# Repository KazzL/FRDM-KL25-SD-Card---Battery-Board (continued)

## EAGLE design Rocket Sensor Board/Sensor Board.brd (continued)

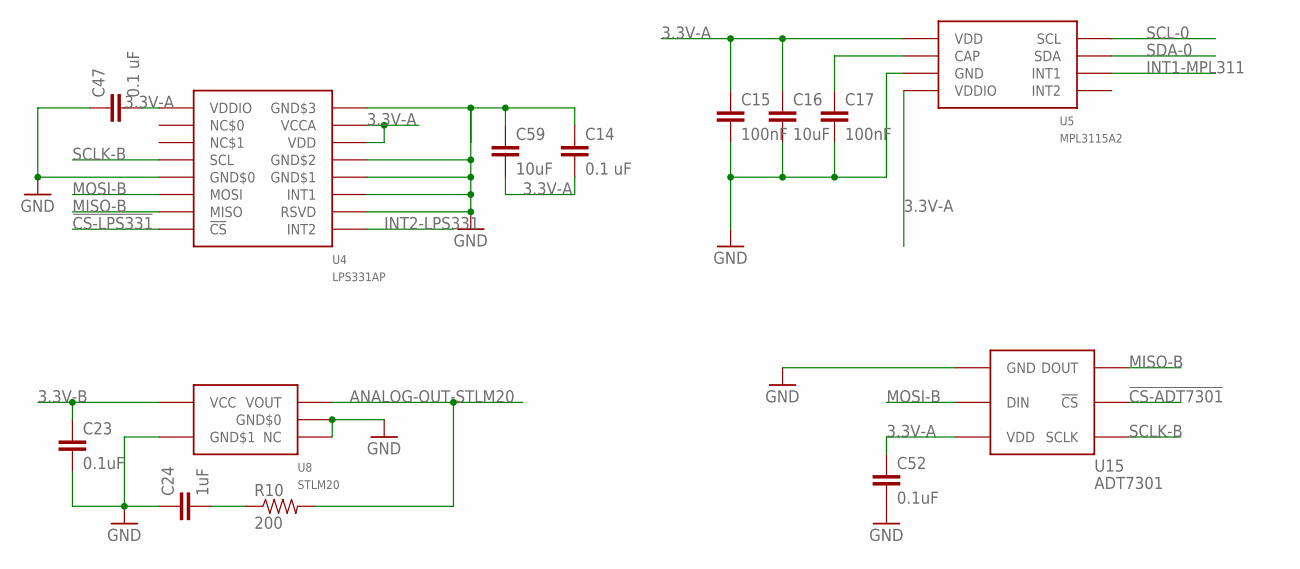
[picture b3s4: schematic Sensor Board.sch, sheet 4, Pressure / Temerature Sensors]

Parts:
C14, C47: 0.1 uF; C0402
C15, C17: 100nF; C0402
C16: 10uF; C0402
C23, C52: 0.1uF; C0402
C24: 1uF; C0402
C59: 10uF; C0603
R10: 200; R0402
U4: LPS331AP; LGA-16(3X3)
U5: MPL3115A2; LGA-8(5X3)
U8: STLM20; SOT323-5L
U15: ADT7301; SOT23-6

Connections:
3.3V-A: C14.2, C15.1, C16.1, C47.2, C52.1, C59.2, U4.P$1 (VDDIO), U4.P$14 (VDD), U4.P$15 (VCCA), U5.P$1 (VDD), U5.P$4 (VDDIO), U15.P$3 (VDD); also elsewhere on the board
3.3V-B: C23.1, U8.P$4 (VCC); also elsewhere on the board
!CS-ADT7301: U15.P$5 (!CS); also elsewhere on the board
!CS-LPS331: U4.P$8 (!CS); also elsewhere on the board
ANALOG-OUT-STLM20: R10.2, U8.P$3 (VOUT); also elsewhere on the board
GND: C14.1, C15.2, C16.2, C17.2, C23.2, C24.1, C47.1, C52.2, C59.1, U4.P$5 (GND$0), U4.P$10 (RSVD), U4.P$11 (INT1), U4.P$12 (GND$1), U4.P$13 (GND$2), U4.P$16 (GND$3), U5.P$3 (GND), U8.P$1 (NC), U8.P$2 (GND$0), U8.P$5 (GND$1), U15.P$1 (GND); also elsewhere on the board
INT1-MPL311: U5.P$6 (INT1); also elsewhere on the board
INT2-LPS331: U4.P$9 (INT2); also elsewhere on the board
MISO-B: U4.P$7 (MISO), U15.P$6 (DOUT); also elsewhere on the board
MOSI-B: U4.P$6 (MOSI), U15.P$2 (DIN); also elsewhere on the board
unnamed: C17.1, U5.P$2 (CAP)
unnamed: C24.2, R10.1
SCL-0: U5.P$8 (SCL); also elsewhere on the board
SCLK-B: U4.P$4 (SCL), U15.P$4 (SCLK); also elsewhere on the board
SDA-0: U5.P$7 (SDA); also elsewhere on the board

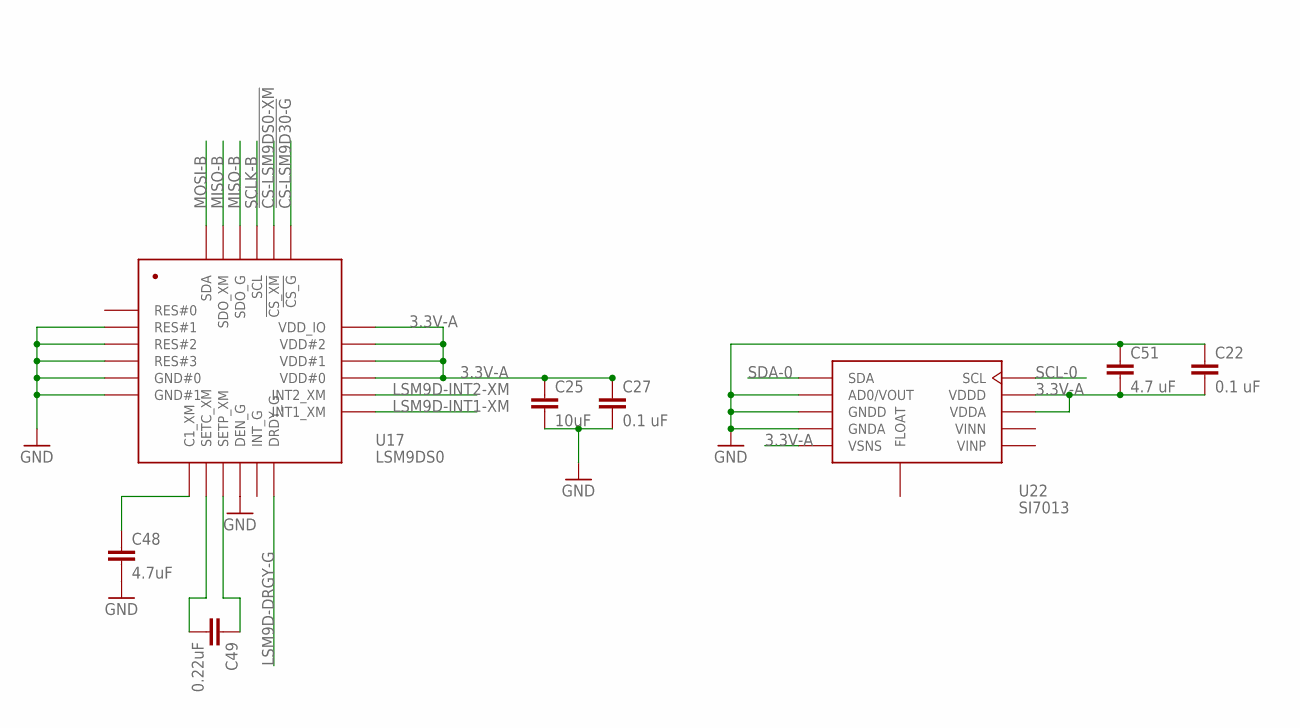
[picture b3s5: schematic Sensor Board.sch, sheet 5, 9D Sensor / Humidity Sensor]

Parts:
C22, C27: 0.1 uF; C0402
C25: 10uF; C0603
C48: 4.7uF; C0603
C49: 0.22uF; C0402
C51: 4.7 uF; C0402
U17: LSM9DS0; LGA-24(4X4)
U22: SI7013; DFN-10(3X3)

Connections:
3.3V-A: C22.2, C25.1, C27.1, C51.2, U17.P$15 (VDD#0), U17.P$16 (VDD#1), U17.P$17 (VDD#2), U17.P$18 (VDD_IO), U22.P$5 (VSNS), U22.P$8 (VDDA), U22.P$9 (VDDD); also elsewhere on the board
!CS-LSM9D30-G: U17.P$19 (!CS_G); also elsewhere on the board
!CS-LSM9DS0-XM: U17.P$20 (!CS_XM); also elsewhere on the board
GND: C22.1, C25.2, C27.2, C48.2, C51.1, U17.P$2 (RES#1), U17.P$3 (RES#2), U17.P$4 (RES#3), U17.P$5 (GND#0), U17.P$6 (GND#1), U17.P$10 (DEN_G), U22.P$2 (AD0/VOUT), U22.P$3 (GNDD), U22.P$4 (GNDA); also elsewhere on the board
LSM9D-DRGY-G: U17.P$12 (DRDY_G); also elsewhere on the board
LSM9D-INT1-XM: U17.P$13 (INT1_XM); also elsewhere on the board
LSM9D-INT2-XM: U17.P$14 (INT2_XM); also elsewhere on the board
MISO-B: U17.P$22 (SDO_G), U17.P$23 (SDO_XM); also elsewhere on the board
MOSI-B: U17.P$24 (SDA); also elsewhere on the board
unnamed: C48.1, U17.P$7 (C1_XM)
unnamed: C49.2, U17.P$8 (SETC_XM)
unnamed: C49.1, U17.P$9 (SETP_XM)
SCL-0: U22.P$10 (SCL); also elsewhere on the board
SCLK-B: U17.P$21 (SCL); also elsewhere on the board
SDA-0: U22.P$1 (SDA); also elsewhere on the board

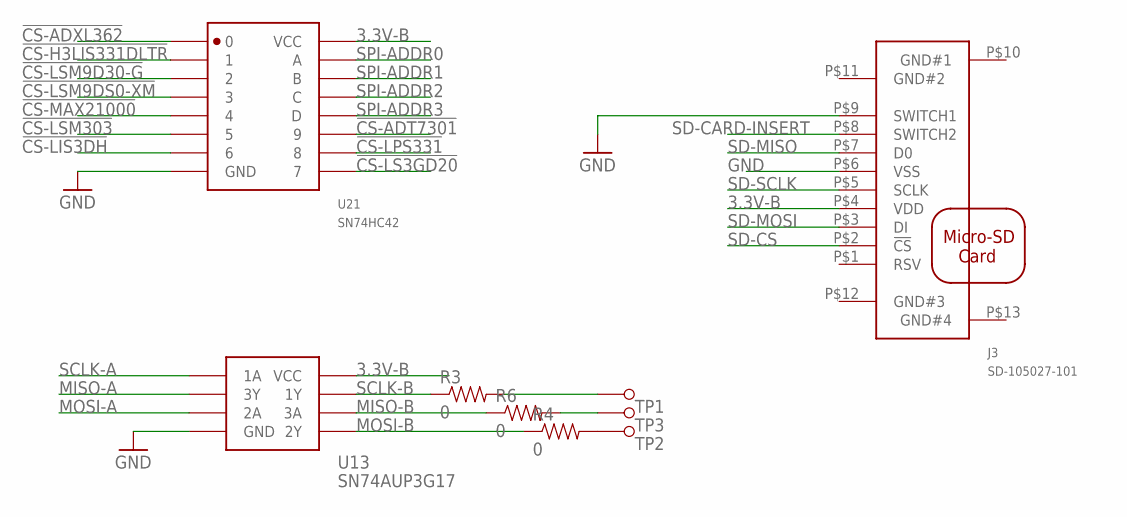
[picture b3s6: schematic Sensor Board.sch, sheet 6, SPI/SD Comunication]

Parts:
J3: SD-105027-101; SD-105027-1001
R3, R4, R6: 0; R0402
TP1, TP2, TP3: TESTPAD(ROUND)
U13: SN74AUP3G17; 8-VFSOP
U21: SN74HC42; SOIC-16

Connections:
3.3V-B: J3.P$4 (VDD), U13.P$8 (VCC), U21.P$16 (VCC); also elsewhere on the board
!CS-ADT7301: U21.P$11 (9); also elsewhere on the board
!CS-ADXL362: U21.P$1 (0); also elsewhere on the board
!CS-H3LIS331DLTR: U21.P$2 (1); also elsewhere on the board
!CS-LIS3DH: U21.P$7 (6); also elsewhere on the board
!CS-LPS331: U21.P$10 (8); also elsewhere on the board
!CS-LS3GD20: U21.P$9 (7); also elsewhere on the board
!CS-LSM9D30-G: U21.P$3 (2); also elsewhere on the board
!CS-LSM9DS0-XM: U21.P$4 (3); also elsewhere on the board
!CS-LSM303: U21.P$6 (5); also elsewhere on the board
!CS-MAX21000: U21.P$5 (4); also elsewhere on the board
GND: J3.P$6 (VSS), J3.P$9 (SWITCH1), U13.P$4 (GND), U21.P$8 (GND); also elsewhere on the board
MISO-A: U13.P$2 (3Y); also elsewhere on the board
MISO-B: R6.1, U13.P$6 (3A); also elsewhere on the board
MOSI-A: U13.P$3 (2A); also elsewhere on the board
MOSI-B: R4.1, U13.P$5 (2Y); also elsewhere on the board
unnamed: R3.2, TP1.P$1
unnamed: R4.2, TP2.P$1
unnamed: R6.2, TP3.P$1
SCLK-A: U13.P$1 (1A); also elsewhere on the board
SCLK-B: R3.1, U13.P$7 (1Y); also elsewhere on the board
SD-CARD-INSERT: J3.P$8 (SWITCH2); also elsewhere on the board
SD-CS: J3.P$2 (!CS); also elsewhere on the board
SD-MISO: J3.P$7 (D0); also elsewhere on the board
SD-MOSI: J3.P$3 (DI); also elsewhere on the board
SD-SCLK: J3.P$5 (SCLK); also elsewhere on the board
SPI-ADDR0: U21.P$15 (A); also elsewhere on the board
SPI-ADDR1: U21.P$14 (B); also elsewhere on the board
SPI-ADDR2: U21.P$13 (C); also elsewhere on the board
SPI-ADDR3: U21.P$12 (D); also elsewhere on the board

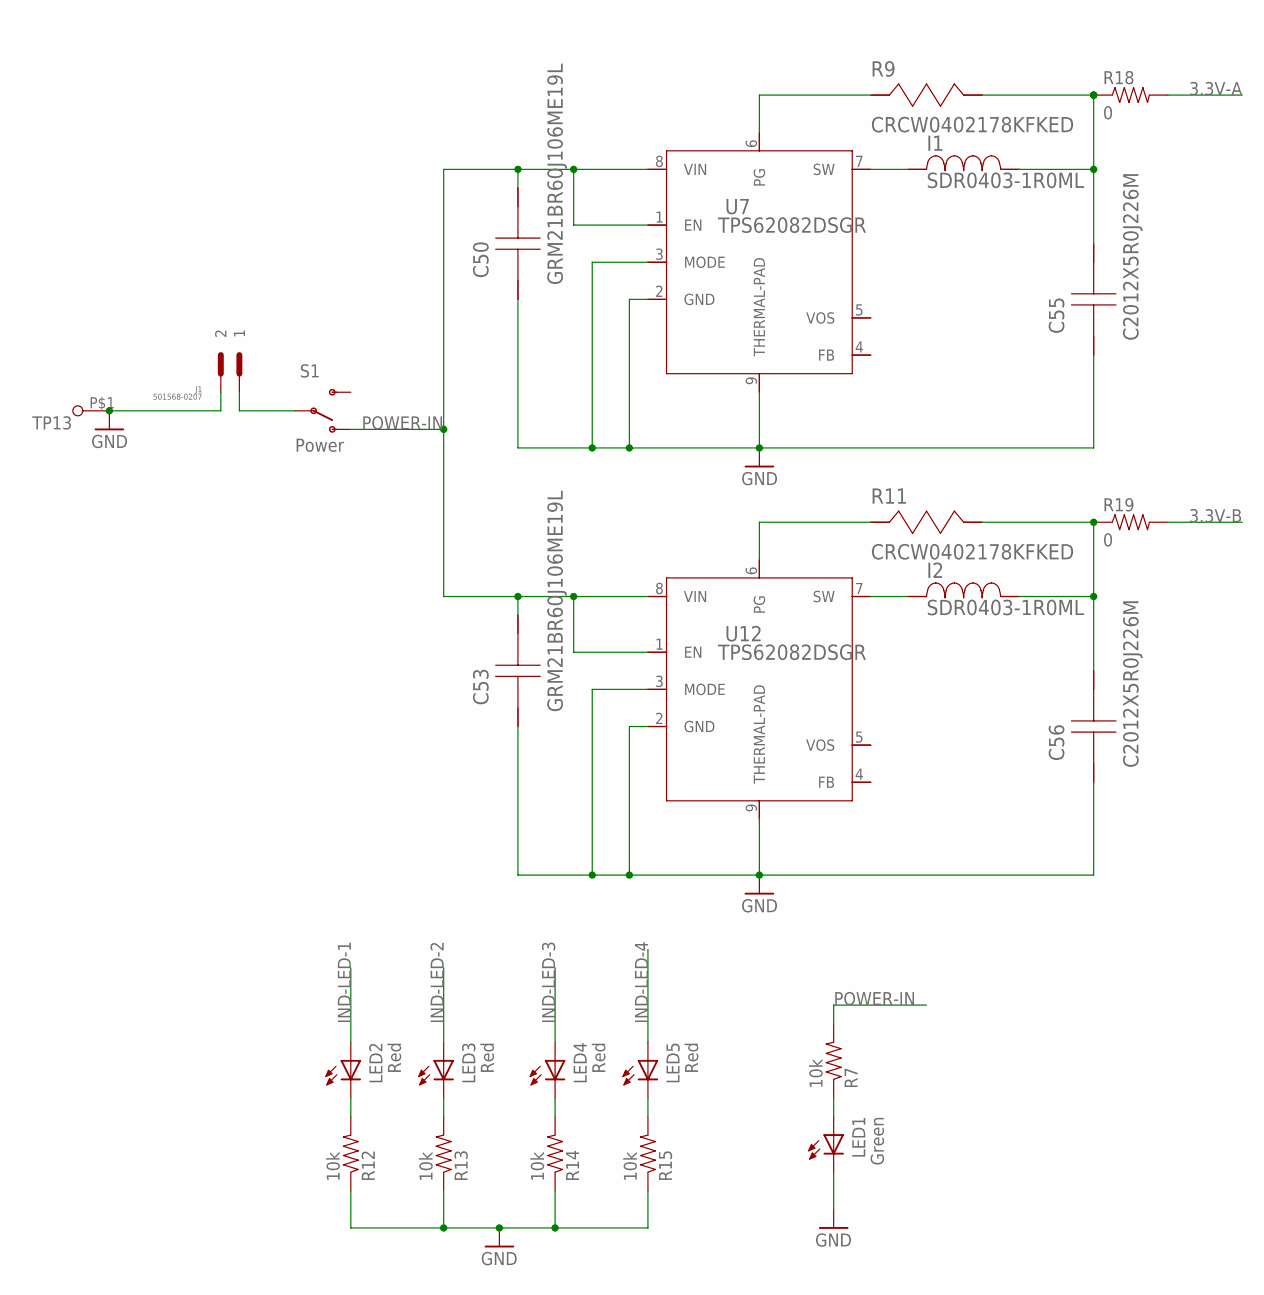
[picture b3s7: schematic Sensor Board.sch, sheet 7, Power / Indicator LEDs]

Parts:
C50, C53: GRM21BR60J106ME19L; 0805
C55, C56: C2012X5R0J226M; 0805
I1, I2: SDR0403-1R0ML; SDR0403
J1: 501568-0207
LED1: Green; LED_0402
LED2, LED3, LED4, LED5: Red; LED_0402
R7, R12, R13, R14, R15: 10k; R0402
R9, R11: CRCW0402178KFKED; 0402
R18, R19: 0; 0603-RES
S1: Power; SWITCH-SPST-SMD-A
TP13: TESTPAD(ROUND)
U7, U12: TPS62082DSGR; S-PWSON-N8

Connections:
3.3V-A: R18.2; also elsewhere on the board
3.3V-B: R19.2; also elsewhere on the board
GND: C50.2, C53.2, C55.2, C56.2, J1.P$2 (2), LED1.C, R12.1, R13.1, R14.1, R15.1, TP13.P$1, U7.2 (GND), U7.3 (MODE), U7.9 (THERMAL-PAD), U12.2 (GND), U12.3 (MODE), U12.9 (THERMAL-PAD); also elsewhere on the board
IND-LED-1: LED2.A; also elsewhere on the board
IND-LED-2: LED3.A; also elsewhere on the board
IND-LED-3: LED4.A; also elsewhere on the board
IND-LED-4: LED5.A; also elsewhere on the board
unnamed: J1.P$1 (1), S1.2
unnamed: I1.2, U7.7 (SW)
unnamed: LED5.C, R15.2
unnamed: C55.1, I1.1, R9.1, R18.1
unnamed: R9.2, U7.6 (PG)
unnamed: C56.1, I2.1, R11.1, R19.1
unnamed: LED1.A, R7.1
unnamed: LED4.C, R14.2
unnamed: LED3.C, R13.2
unnamed: LED2.C, R12.2
unnamed: I2.2, U12.7 (SW)
unnamed: R11.2, U12.6 (PG)
POWER-IN: C50.1, C53.1, R7.2, S1.1 (O), U7.1 (EN), U7.8 (VIN), U12.1 (EN), U12.8 (VIN)

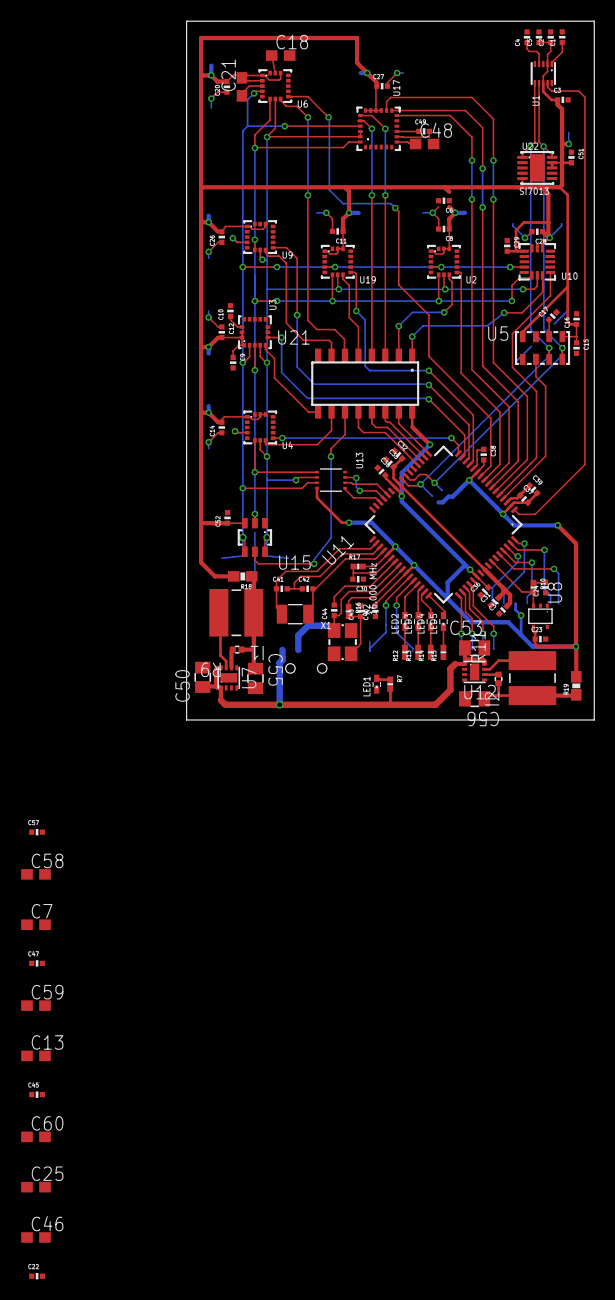
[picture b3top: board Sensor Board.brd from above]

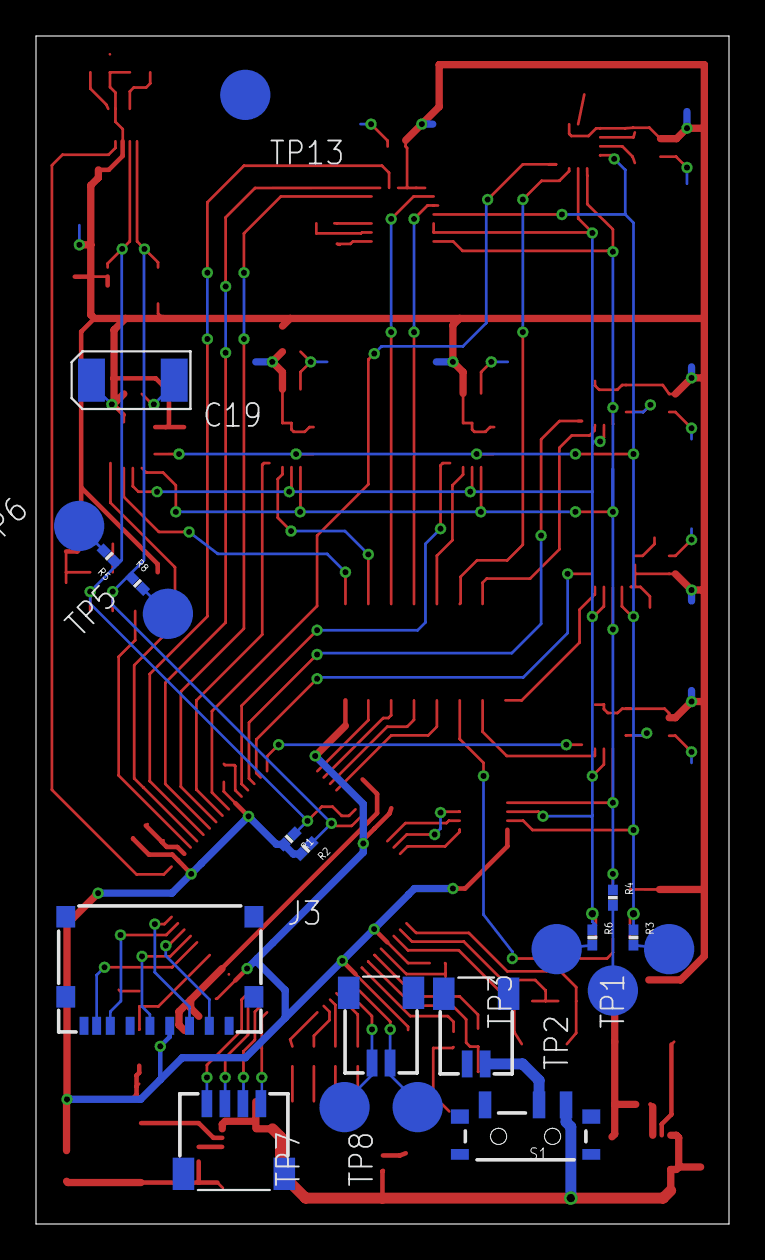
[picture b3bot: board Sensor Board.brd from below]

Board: 4 copper layers, 38.5 x 66.0 mm, 118 parts (21 on the bottom side), 89 nets.

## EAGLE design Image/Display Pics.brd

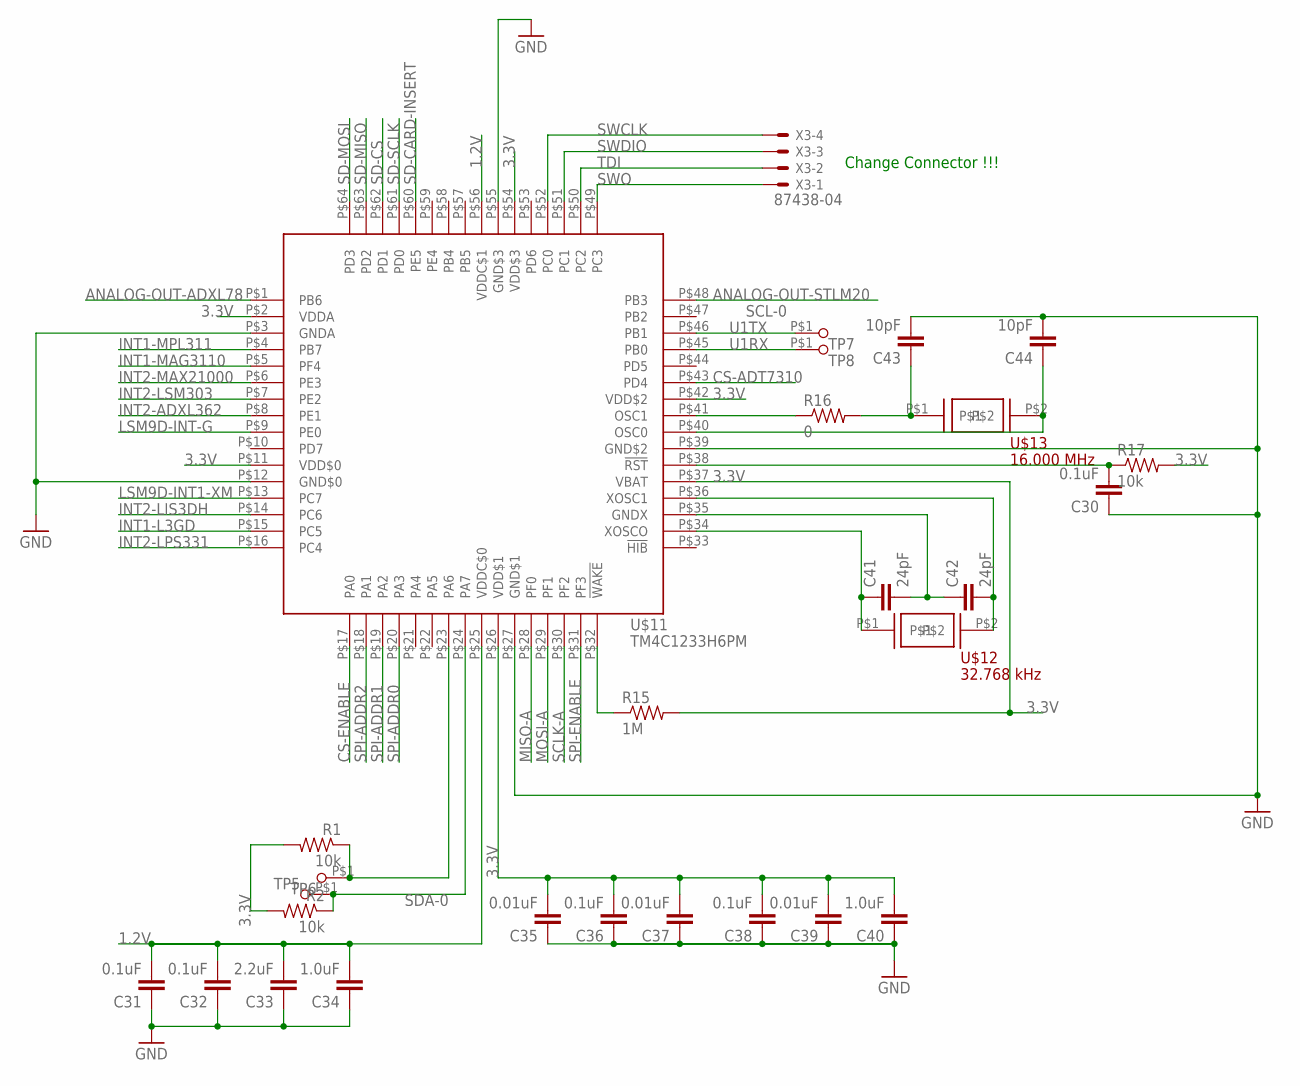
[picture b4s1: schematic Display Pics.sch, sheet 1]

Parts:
C30, C31, C32, C36, C38: 0.1uF; 0402-CAP
C33: 2.2uF; 0402-CAP
C34, C40: 1.0uF; 0402-CAP
C35, C37, C39: 0.01uF; 0402-CAP
C41, C42: 24pF; 0402-CAP
C43, C44: 10pF; 0402-CAP
R1, R2, R17: 10k; 0402-RES
R15: 1M; 0402-RES
R16: 0; 0402-RES
TP5, TP6, TP7, TP8: TESTPAD(ROUND)
U$11: TM4C1233H6PM; S-PQFP-G64
U$12: 32.768 kHz; CYLINDRICAL-(1.9DIAX6L)
U$13: 16.000 MHz; 2-SMD
X3: 87438-04

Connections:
1.2V: C31.2, C32.2, C33.2, C34.2, U$11.P$25 (VDDC$0), U$11.P$56 (VDDC$1); also elsewhere on the board
3.3V: C35.2, C36.2, C37.2, C38.2, C39.2, C40.2, R1.2, R2.2, R15.2, R17.2, U$11.P$2 (VDDA), U$11.P$11 (VDD$0), U$11.P$26 (VDD$1), U$11.P$37 (VBAT), U$11.P$42 (VDD$2), U$11.P$54 (VDD$3); also elsewhere on the board
ANALOG-OUT-ADXL78: U$11.P$1 (PB6); also elsewhere on the board
ANALOG-OUT-STLM20: U$11.P$48 (PB3); also elsewhere on the board
CS-ADT7310: U$11.P$43 (PD4); also elsewhere on the board
CS-ENABLE: U$11.P$17 (PA0); also elsewhere on the board
GND: C30.1, C31.1, C32.1, C33.1, C34.1, C35.1, C36.1, C37.1, C38.1, C39.1, C40.1, C43.2, C44.2, U$11.P$3 (GNDA), U$11.P$12 (GND$0), U$11.P$27 (GND$1), U$11.P$39 (GND$2), U$11.P$55 (GND$3); also elsewhere on the board
INT1-L3GD: U$11.P$15 (PC5); also elsewhere on the board
INT1-MAG3110: U$11.P$5 (PF4); also elsewhere on the board
INT1-MPL311: U$11.P$4 (PB7); also elsewhere on the board
INT2-ADXL362: U$11.P$8 (PE1); also elsewhere on the board
INT2-LIS3DH: U$11.P$14 (PC6); also elsewhere on the board
INT2-LPS331: U$11.P$16 (PC4); also elsewhere on the board
INT2-LSM303: U$11.P$7 (PE2); also elsewhere on the board
INT2-MAX21000: U$11.P$6 (PE3); also elsewhere on the board
LSM9D-INT1-XM: U$11.P$13 (PC7); also elsewhere on the board
LSM9D-INT-G: U$11.P$9 (PE0); also elsewhere on the board
MISO-A: U$11.P$28 (PF0); also elsewhere on the board
MOSI-A: U$11.P$29 (PF1)
unnamed: C30.2, R17.1, U$11.P$38 (!RST)
unnamed: C42.2, U$11.P$36 (XOSC1), U$12.P$2
unnamed: C41.1, U$11.P$34 (XOSCO), U$12.P$1
unnamed: C41.2, C42.1, U$11.P$35 (GNDX)
unnamed: C43.1, R16.2, U$13.P$1
unnamed: C44.1, U$11.P$40 (OSC0), U$13.P$2
unnamed: R16.1, U$11.P$41 (OSC1)
unnamed: R15.1, U$11.P$32 (!WAKE)
SCL-0: R1.1, TP6.P$1, U$11.P$23 (PA6); also elsewhere on the board
SCLK-A: U$11.P$30 (PF2); also elsewhere on the board
SD-CARD-INSERT: U$11.P$60 (PE5); also elsewhere on the board
SD-CS: U$11.P$62 (PD1); also elsewhere on the board
SD-MISO: U$11.P$63 (PD2); also elsewhere on the board
SD-MOSI: U$11.P$64 (PD3); also elsewhere on the board
SD-SCLK: U$11.P$61 (PD0); also elsewhere on the board
SDA-0: R2.1, TP5.P$1, U$11.P$24 (PA7); also elsewhere on the board
SPI-ADDR0: U$11.P$20 (PA3); also elsewhere on the board
SPI-ADDR1: U$11.P$19 (PA2); also elsewhere on the board
SPI-ADDR2: U$11.P$18 (PA1); also elsewhere on the board
SPI-ENABLE: U$11.P$31 (PF3); also elsewhere on the board
SWCLK: U$11.P$52 (PC0), X3.4
SWDIO: U$11.P$51 (PC1), X3.3
SWO: U$11.P$49 (PC3), X3.1
TDI: U$11.P$50 (PC2), X3.2
U1RX: TP8.P$1, U$11.P$45 (PB0)
U1TX: TP7.P$1, U$11.P$46 (PB1)

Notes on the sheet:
Change Connector !!!

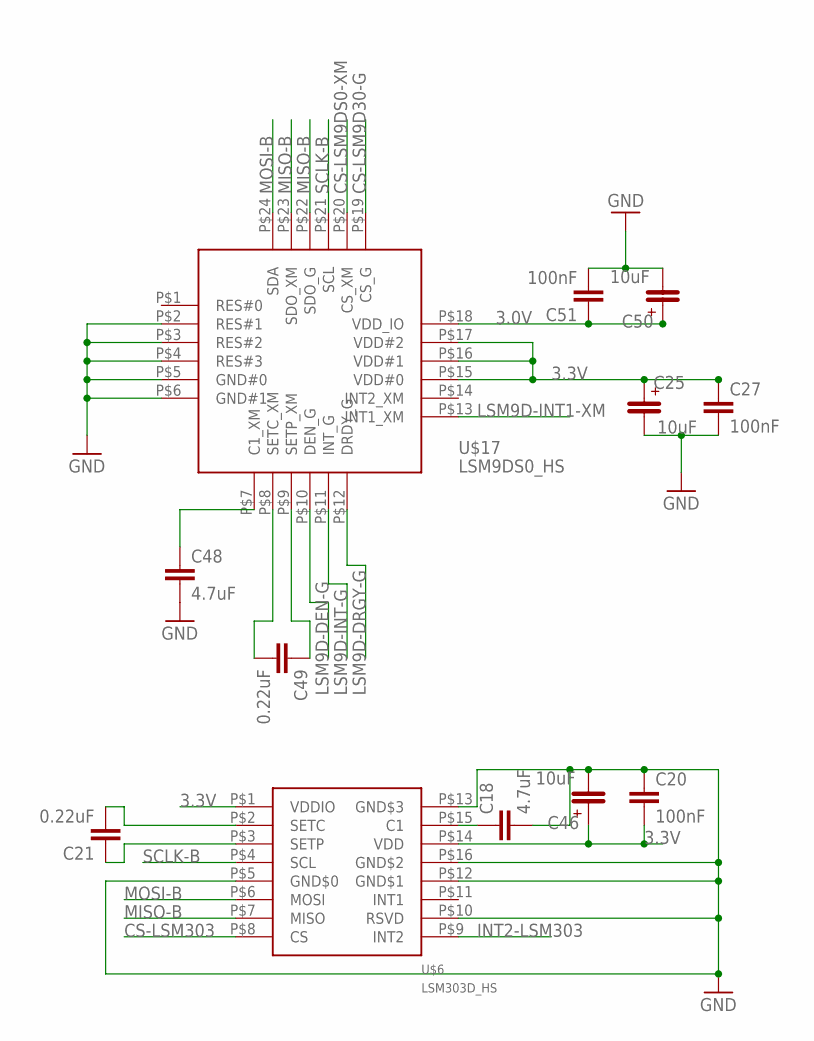
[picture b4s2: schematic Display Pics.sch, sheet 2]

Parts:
C18, C48: 4.7uF; 0402-CAP
C20, C27, C51: 100nF; 0402-CAP
C21, C49: 0.22uF; 0402-CAP
C25, C46, C50: 10uF; 4.3X7.3SMD
U$6: LSM303D_HS; LGA-16(3X3)_HS
U$17: LSM9DS0_HS; LGA-24(4X4)_HS

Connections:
3.0V: C50.P$1, C51.1, U$17.P$18 (VDD_IO); also elsewhere on the board
3.3V: C20.2, C25.P$1, C27.1, C46.P$1, U$6.P$1 (VDDIO), U$6.P$14 (VDD), U$17.P$15 (VDD#0), U$17.P$16 (VDD#1), U$17.P$17 (VDD#2); also elsewhere on the board
CS-LSM9D30-G: U$17.P$19 (CS_G); also elsewhere on the board
CS-LSM9DS0-XM: U$17.P$20 (CS_XM); also elsewhere on the board
CS-LSM303: U$6.P$8 (CS); also elsewhere on the board
GND: C18.2, C20.1, C25.P$2, C27.2, C46.P$2, C48.2, C50.P$2, C51.2, U$6.P$5 (GND$0), U$6.P$10 (RSVD), U$6.P$12 (GND$1), U$6.P$13 (GND$3), U$6.P$16 (GND$2), U$17.P$2 (RES#1), U$17.P$3 (RES#2), U$17.P$4 (RES#3), U$17.P$5 (GND#0), U$17.P$6 (GND#1); also elsewhere on the board
INT2-LSM303: U$6.P$9 (INT2); also elsewhere on the board
LSM9D-DEN-G: U$17.P$10 (DEN_G)
LSM9D-DRGY-G: U$17.P$12 (DRDY_G)
LSM9D-INT1-XM: U$17.P$13 (INT1_XM); also elsewhere on the board
LSM9D-INT-G: U$17.P$11 (INT_G); also elsewhere on the board
MISO-B: U$6.P$7 (MISO), U$17.P$22 (SDO_G), U$17.P$23 (SDO_XM); also elsewhere on the board
MOSI-B: U$6.P$6 (MOSI), U$17.P$24 (SDA); also elsewhere on the board
unnamed: C18.1, U$6.P$15 (C1)
unnamed: C21.2, U$6.P$2 (SETC)
unnamed: C48.1, U$17.P$7 (C1_XM)
unnamed: C21.1, U$6.P$3 (SETP)
unnamed: C49.2, U$17.P$8 (SETC_XM)
unnamed: C49.1, U$17.P$9 (SETP_XM)
SCLK-B: U$6.P$4 (SCL), U$17.P$21 (SCL); also elsewhere on the board

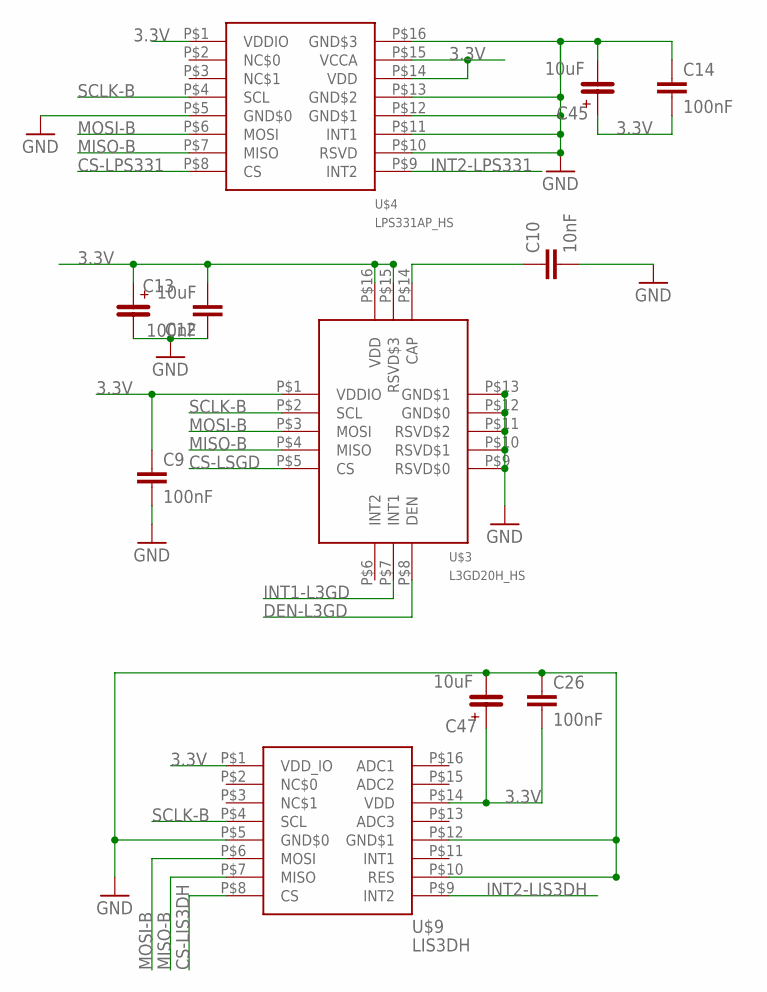
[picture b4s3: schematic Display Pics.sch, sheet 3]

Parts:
C9, C14, C26: 100nF; 0402-CAP
C10: 10nF; 0402-CAP
C12: 10uF; 0402-CAP
C13: 100nF; 4.3X7.3SMD
C45, C47: 10uF; 4.3X7.3SMD
U$3: L3GD20H_HS; LGA-16(3X3)_HS
U$4: LPS331AP_HS; LGA-16(3X3)_HS
U$9: LIS3DH; LGA-16(3X3)_HS

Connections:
3.3V: C9.1, C12.2, C13.P$1, C14.2, C26.2, C45.P$1, C47.P$1, U$3.P$1 (VDDIO), U$3.P$15 (RSVD$3), U$3.P$16 (VDD), U$4.P$1 (VDDIO), U$4.P$14 (VDD), U$4.P$15 (VCCA), U$9.P$1 (VDD_IO), U$9.P$14 (VDD); also elsewhere on the board
CS-LIS3DH: U$9.P$8 (CS); also elsewhere on the board
CS-LPS331: U$4.P$8 (CS); also elsewhere on the board
CS-LSGD: U$3.P$5 (CS); also elsewhere on the board
DEN-L3GD: U$3.P$8 (DEN)
GND: C9.2, C10.2, C12.1, C13.P$2, C14.1, C26.1, C45.P$2, C47.P$2, U$3.P$9 (RSVD$0), U$3.P$10 (RSVD$1), U$3.P$11 (RSVD$2), U$3.P$12 (GND$0), U$3.P$13 (GND$1), U$4.P$5 (GND$0), U$4.P$10 (RSVD), U$4.P$11 (INT1), U$4.P$12 (GND$1), U$4.P$13 (GND$2), U$4.P$16 (GND$3), U$9.P$5 (GND$0), U$9.P$10 (RES), U$9.P$12 (GND$1); also elsewhere on the board
INT1-L3GD: U$3.P$7 (INT1); also elsewhere on the board
INT2-LIS3DH: U$9.P$9 (INT2); also elsewhere on the board
INT2-LPS331: U$4.P$9 (INT2); also elsewhere on the board
MISO-B: U$3.P$4 (MISO), U$4.P$7 (MISO), U$9.P$7 (MISO); also elsewhere on the board
MOSI-B: U$3.P$3 (MOSI), U$4.P$6 (MOSI), U$9.P$6 (MOSI); also elsewhere on the board
unnamed: C10.1, U$3.P$14 (CAP)
SCLK-B: U$3.P$2 (SCL), U$4.P$4 (SCL), U$9.P$4 (SCL); also elsewhere on the board

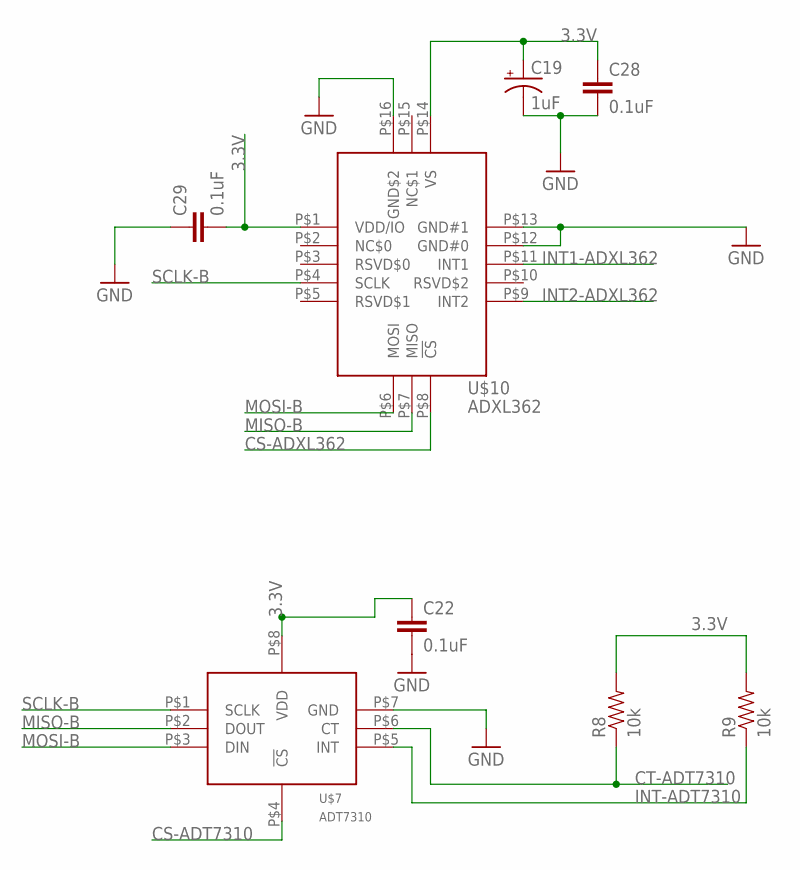
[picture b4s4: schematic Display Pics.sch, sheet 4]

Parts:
C19: 1uF; EIA6032
C22, C28, C29: 0.1uF; 0402-CAP
R8, R9: 10k; 0402-RES
U$7: ADT7310; SOIC-8(5X6.2)
U$10: ADXL362; LGA-16(3X3.25)_HS

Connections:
3.3V: C19.P$1 (+), C22.1, C28.1, C29.2, R8.2, R9.2, U$7.P$8 (VDD), U$10.P$1 (VDD/IO), U$10.P$14 (VS); also elsewhere on the board
CS-ADT7310: U$7.P$4 (!CS); also elsewhere on the board
CS-ADXL362: U$10.P$8 (!CS); also elsewhere on the board
CT-ADT7310: R8.1, U$7.P$6 (CT)
GND: C19.P$2 (-), C22.2, C28.2, C29.1, U$7.P$7 (GND), U$10.P$12 (GND#0), U$10.P$13 (GND#1), U$10.P$16 (GND$2); also elsewhere on the board
INT1-ADXL362: U$10.P$11 (INT1)
INT2-ADXL362: U$10.P$9 (INT2); also elsewhere on the board
INT-ADT7310: R9.1, U$7.P$5 (INT)
MISO-B: U$7.P$2 (DOUT), U$10.P$7 (MISO); also elsewhere on the board
MOSI-B: U$7.P$3 (DIN), U$10.P$6 (MOSI); also elsewhere on the board
SCLK-B: U$7.P$1 (SCLK), U$10.P$4 (SCLK); also elsewhere on the board

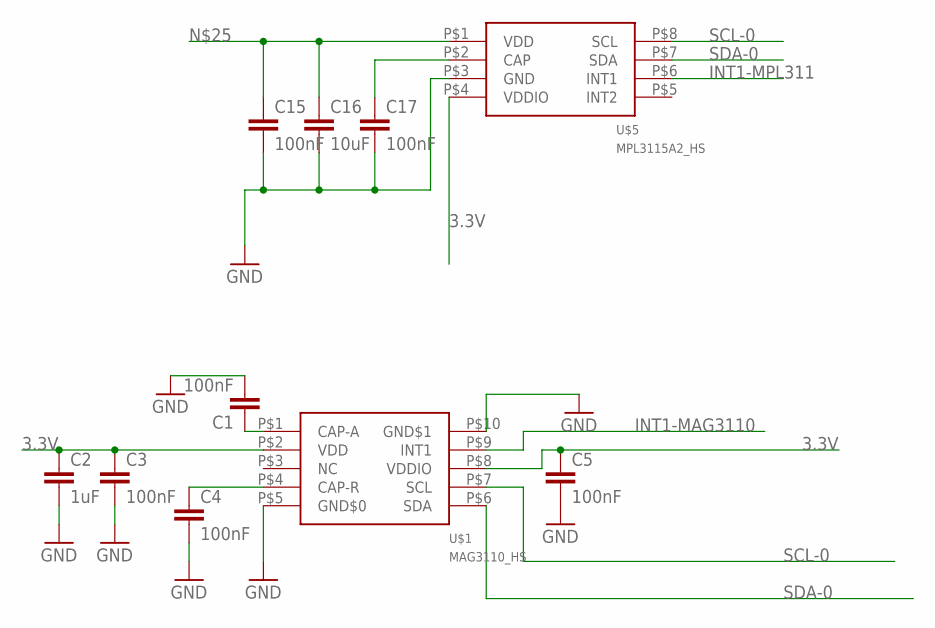
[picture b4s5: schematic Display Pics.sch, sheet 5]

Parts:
C1, C3, C4, C5, C15, C17: 100nF; 0402-CAP
C2: 1uF; 0402-CAP
C16: 10uF; 0402-CAP
U$1: MAG3110_HS; DFN-10(2X2)_HS
U$5: MPL3115A2_HS; LGA-8(5X3)_HS

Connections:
3.3V: C2.1, C3.1, C5.1, U$1.P$2 (VDD), U$1.P$8 (VDDIO), U$5.P$4 (VDDIO); also elsewhere on the board
GND: C1.2, C2.2, C3.2, C4.2, C5.2, C15.2, C16.2, C17.2, U$1.P$5 (GND$0), U$1.P$10 (GND$1), U$5.P$3 (GND); also elsewhere on the board
INT1-MAG3110: U$1.P$9 (INT1); also elsewhere on the board
INT1-MPL311: U$5.P$6 (INT1); also elsewhere on the board
unnamed: C1.1, U$1.P$1 (CAP-A)
unnamed: C4.1, U$1.P$4 (CAP-R)
unnamed: C17.1, U$5.P$2 (CAP)
unnamed: C15.1, C16.1, U$5.P$1 (VDD)
SCL-0: U$1.P$7 (SCL), U$5.P$8 (SCL); also elsewhere on the board
SDA-0: U$1.P$6 (SDA), U$5.P$7 (SDA); also elsewhere on the board

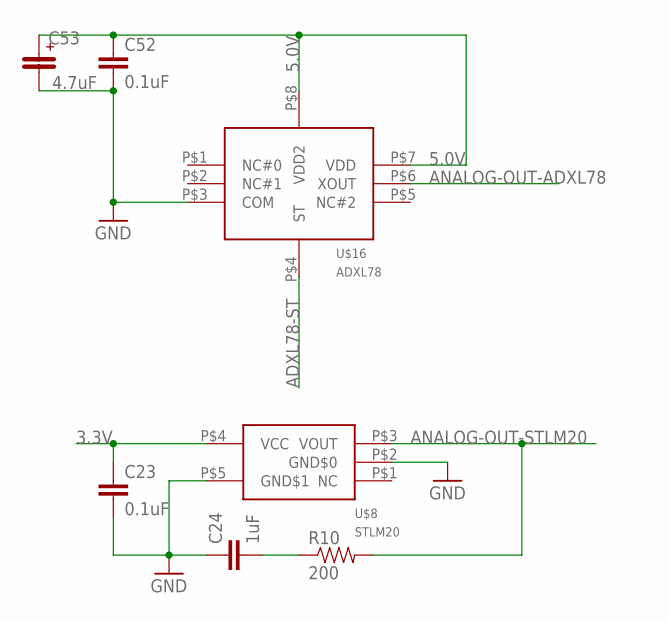
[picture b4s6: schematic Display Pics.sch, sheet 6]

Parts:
C23, C52: 0.1uF; 0402-CAP
C24: 1uF; 0402-CAP
C53: 4.7uF; 4.3X7.3SMD
R10: 200; 0402-RES
U$8: STLM20; SOT323-5L
U$16: ADXL78; LCC-8(5X5)_HS

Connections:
3.3V: C23.1, U$8.P$4 (VCC); also elsewhere on the board
5.0V: C52.1, C53.P$1, U$16.P$7 (VDD), U$16.P$8 (VDD2); also elsewhere on the board
ADXL78-ST: U$16.P$4 (ST)
ANALOG-OUT-ADXL78: U$16.P$6 (XOUT); also elsewhere on the board
ANALOG-OUT-STLM20: R10.2, U$8.P$3 (VOUT); also elsewhere on the board
GND: C23.2, C24.1, C52.2, C53.P$2, U$8.P$2 (GND$0), U$8.P$5 (GND$1), U$16.P$3 (COM); also elsewhere on the board
unnamed: C24.2, R10.1

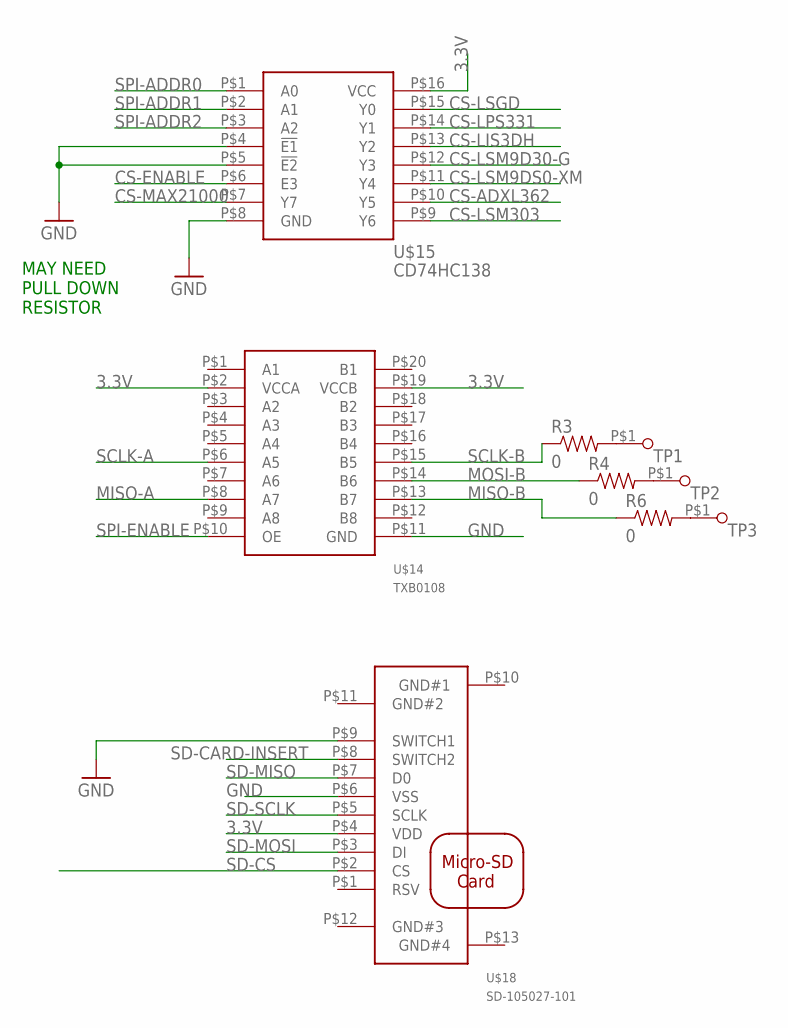
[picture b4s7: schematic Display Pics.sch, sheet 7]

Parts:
R3, R4, R6: 0; 0402-RES
TP1, TP2, TP3: TESTPAD(ROUND)
U$14: TXB0108; TSSOP-(PW)-20
U$15: CD74HC138; SOIC-16
U$18: SD-105027-101

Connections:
3.3V: U$14.P$2 (VCCA), U$14.P$19 (VCCB), U$15.P$16 (VCC), U$18.P$4 (VDD); also elsewhere on the board
CS-ADXL362: U$15.P$10 (Y5); also elsewhere on the board
CS-ENABLE: U$15.P$6 (E3); also elsewhere on the board
CS-LIS3DH: U$15.P$13 (Y2); also elsewhere on the board
CS-LPS331: U$15.P$14 (Y1); also elsewhere on the board
CS-LSGD: U$15.P$15 (Y0); also elsewhere on the board
CS-LSM9D30-G: U$15.P$12 (Y3); also elsewhere on the board
CS-LSM9DS0-XM: U$15.P$11 (Y4); also elsewhere on the board
CS-LSM303: U$15.P$9 (Y6); also elsewhere on the board
CS-MAX21000: U$15.P$7 (Y7); also elsewhere on the board
GND: U$14.P$11 (GND), U$15.P$4 (!E1), U$15.P$5 (!E2), U$15.P$8 (GND), U$18.P$6 (VSS), U$18.P$9 (SWITCH1); also elsewhere on the board
MISO-A: U$14.P$8 (A7); also elsewhere on the board
MISO-B: R6.1, U$14.P$13 (B7); also elsewhere on the board
MOSI-B: R4.1, U$14.P$14 (B6); also elsewhere on the board
unnamed: R3.2, TP1.P$1
unnamed: R4.2, TP2.P$1
unnamed: R6.2, TP3.P$1
SCLK-A: U$14.P$6 (A5); also elsewhere on the board
SCLK-B: R3.1, U$14.P$15 (B5); also elsewhere on the board
SD-CARD-INSERT: U$18.P$8 (SWITCH2); also elsewhere on the board
SD-CS: U$18.P$2 (CS); also elsewhere on the board
SD-MISO: U$18.P$7 (D0); also elsewhere on the board
SD-MOSI: U$18.P$3 (DI); also elsewhere on the board
SD-SCLK: U$18.P$5 (SCLK); also elsewhere on the board
SPI-ADDR0: U$15.P$1 (A0); also elsewhere on the board
SPI-ADDR1: U$15.P$2 (A1); also elsewhere on the board
SPI-ADDR2: U$15.P$3 (A2); also elsewhere on the board
SPI-ENABLE: U$14.P$10 (OE); also elsewhere on the board

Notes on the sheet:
MAY NEED PULL DOWN RESISTOR

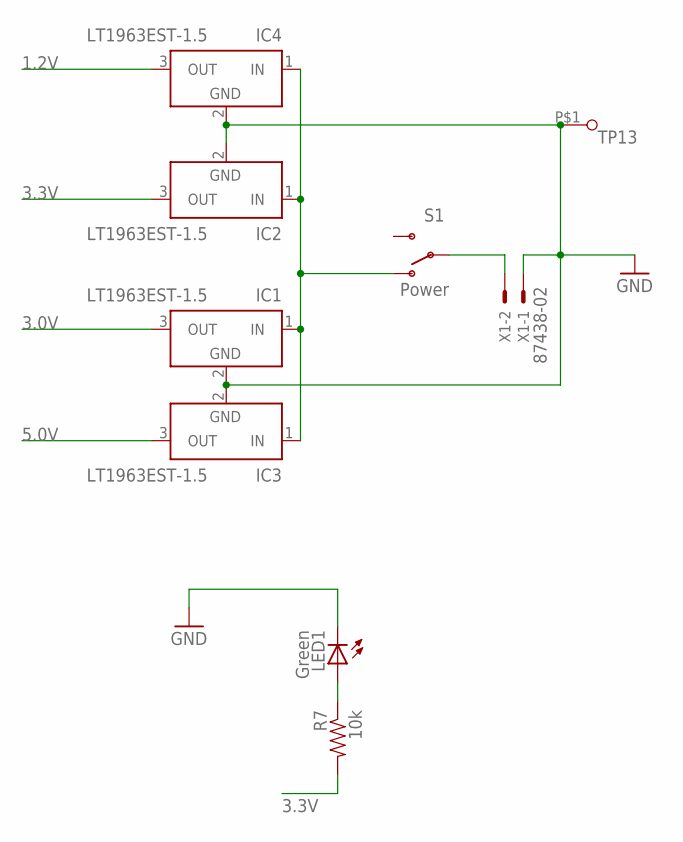
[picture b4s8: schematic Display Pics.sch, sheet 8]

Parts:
IC1, IC2, IC3, IC4: LT1963EST-1.5; SOT223
LED1: Green; LED_SML0603
R7: 10k; 0402-RES
S1: Power; SWITCH-SPST-SMD-A
TP13: TESTPAD(ROUND)
X1: 87438-02

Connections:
1.2V: IC4.3 (OUT); also elsewhere on the board
3.0V: IC1.3 (OUT); also elsewhere on the board
3.3V: IC2.3 (OUT), R7.2; also elsewhere on the board
5.0V: IC3.3 (OUT); also elsewhere on the board
GND: IC1.2 (GND), IC1.4 (GND), IC2.2 (GND), IC2.4 (GND), IC3.2 (GND), IC3.4 (GND), IC4.2 (GND), IC4.4 (GND), LED1.C, TP13.P$1, X1.1; also elsewhere on the board
unnamed: S1.2, X1.2
unnamed: IC1.1 (IN), IC2.1 (IN), IC3.1 (IN), IC4.1 (IN), S1.1 (O)
unnamed: LED1.A, R7.1

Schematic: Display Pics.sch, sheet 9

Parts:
C11: CAPACITOR; 0402-CAP
C54: EEFCD0J100ER; 4.3X7.3SMD
U$19: MAX21000_HS; LGA-16(3X3)_HS

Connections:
3.3V: C11.1, C54.P$1, U$19.P$14 (VDD#0), U$19.P$15 (VDD#1); also elsewhere on the board
CS-MAX21000: U$19.P$8 (CS); also elsewhere on the board
GND: C11.2, C54.P$2, U$19.P$5 (GND); also elsewhere on the board
INT2-MAX21000: U$19.P$9 (INT2); also elsewhere on the board
MISO-B: U$19.P$7 (MISO); also elsewhere on the board
MOSI-B: U$19.P$6 (MOSI); also elsewhere on the board
SCLK-B: U$19.P$4 (SCLK); also elsewhere on the board

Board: 2 copper layers, 97 parts (0 on the bottom side), 77 nets, no tracks yet.
